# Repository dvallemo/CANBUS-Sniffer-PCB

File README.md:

# CANBUS Sniffer PCB

A compact **USB-to-CAN Bus interface** designed around an **STM32F0 microcontroller** and a **CAN transceiver**. This project was built to practice professional PCB design techniques from schematic capture through PCB layout while following industry design practices.

**Version:** V1.0.0

---

# Features

- USB Type-C Interface
- STM32F0 Microcontroller
- CAN Bus Transceiver
- USB 2.0 Full-Speed Differential Pair
- 3.3V Linear Regulator
- TVS Protection
- Reverse Polarity Protection
- Power LEDs
- CAN Activity LEDs
- SWD Programming Header
- RESET Button
- BOOT Button
- Four Mounting Holes
- Four-Layer PCB

---

# Project Images

## PCB Layout with Ground Pours

---

## 3D Render with Ground Pours

---

## Schematic

---

## Routed PCB

---

## 3D Render

---

# Overview

The goal of this project was to design a complete CAN Bus Sniffer PCB using KiCad while applying professional hardware engineering methodologies.

The board receives power over USB Type-C, regulates the voltage to 3.3V, communicates over a CAN transceiver, and provides an SWD interface for programming and debugging.

Rather than only creating a working PCB, this project focused heavily on layout quality, manufacturability, and signal integrity.

Topics practiced include:

- PCB floorplanning
- Component placement
- USB differential pair routing
- Controlled impedance routing
- Four-layer PCB stackup
- Power distribution
- Ground plane implementation
- Decoupling capacitor placement
- EMI reduction techniques
- Design Rule Checks (DRC)
- Design for Manufacturability (DFM)
- Design for Assembly (DFA)

---

# Hardware Specifications

| Item | Specification |
|------|---------------|
| Microcontroller | STM32F0 Series |
| CAN Transceiver | SN65HVD230 Compatible |
| USB | USB Type-C (USB 2.0 Full Speed) |
| Input Voltage | 5V USB |
| Output Voltage | 3.3V |
| PCB Layers | 4 |
| PCB Thickness | 1.6 mm |
| USB Routing | Controlled Impedance Differential Pair |

---

# PCB Stackup

### Layer 1
- Components
- Signal Routing
- USB Differential Pair

### Layer 2
- Solid Ground Plane

### Layer 3
- Solid Ground Plane

### Layer 4
- Signal Routing
- Power Routing

Using two dedicated internal ground planes provides:

- Continuous return paths
- Reduced EMI
- Improved signal integrity
- Lower ground impedance
- Better high-frequency performance
- Improved power distribution

---

# Engineering Design Decisions

## USB Type-C

USB Type-C was selected for modern compatibility and ease of use.

USB CC pull-down resistors were implemented to correctly identify the board as a USB device.

The USB D+ and D− lines were routed as a differential pair using KiCad's differential pair router.

Special attention was given to:

- Matched trace lengths
- Constant spacing
- Controlled impedance
- Minimal discontinuities
- Smooth routing
- Short path between the connector and downstream circuitry

---

## Differential Pair Routing

Although USB Full-Speed is more forgiving than USB High-Speed, the layout follows professional differential routing practices.

Design considerations included:

- Constant differential spacing
- Matched lengths
- 45° bends
- Minimal skew
- No unnecessary vias
- Short routing distance
- Continuous reference plane underneath the pair

---

## Power Architecture

Power flow:

```text
USB Type-C
    ↓
Protection Circuit
    ↓
Filtering
    ↓
3.3V LDO
    ↓
STM32 + CAN Transceiver
```

Wide power traces were used where appropriate to reduce voltage drop and improve current handling.

---

## Power Integrity

Each power pin is locally decoupled with ceramic capacitors placed as close as possible to the corresponding IC supply pins.

This reduces:

- Supply noise
- Voltage ripple
- Transient voltage drops
- EMI

---

## Grounding Strategy

The board utilizes:

- Layer 2 Solid Ground Plane
- Layer 3 Solid Ground Plane
- Top Ground Pour
- Bottom Ground Pour
- Ground stitching vias

This creates low-impedance return paths and improves signal integrity throughout the design.

The exposed thermal pad underneath the STM32 is connected directly into the internal ground planes through a thermal via.

---

## CAN Interface

The CAN transceiver converts the MCU CAN peripheral into differential CANH and CANL signals suitable for automotive communication.

The layout emphasizes:

- Short routing
- Clean return paths
- Differential signaling
- Noise immunity

---

## Crystal Oscillator

The crystal and its load capacitors were placed immediately adjacent to the MCU oscillator pins.

This minimizes:

- Loop area
- EMI susceptibility
- Clock jitter

---

## Component Placement

Components were grouped by function:

### USB Section
- USB Connector
- ESD Protection
- CC Resistors

### Power Section
- Protection
- LDO
- Filtering
- LEDs

### CAN Section
- CAN Connector
- CAN Transceiver
- Termination Components

### MCU Section
- STM32
- Crystal
- Decoupling
- Programming Header

Keeping functional blocks together improves routing quality and simplifies debugging.

---

# PCB Design Practices

The layout follows several common PCB design guidelines:

- Functional component grouping
- Short decoupling connections
- Short crystal routing
- Controlled impedance USB routing
- Wide power traces
- Ground stitching
- Clean routing
- Minimal unnecessary vias
- Four-layer stackup
- Continuous reference planes
- Full Design Rule Check verification

---

# Software Used

- KiCad 9
- STM32CubeMX
- STM32CubeIDE

---

# Current Status

- ✅ Schematic Complete
- ✅ PCB Layout Complete
- ✅ Four-Layer PCB
- ✅ USB Differential Pair Routed
- ✅ Ground Planes Implemented
- ✅ Design Rule Check Passed
- ✅ 3D Model Generated
- ✅ GitHub Documentation Complete

---

# Future Improvements

- PCB Manufacturing
- Board Bring-up
- Firmware Development
- USB CDC Interface
- CAN Frame Decoder
- Desktop GUI
- Oscilloscope Validation
- Enclosure Design

---

# Lessons Learned

This project provided hands-on experience with:

- USB Type-C hardware implementation
- Controlled impedance routing
- Differential pair routing
- Four-layer PCB stackups
- Ground plane design
- Decoupling strategies
- CAN Bus hardware
- STM32 hardware design
- PCB floorplanning
- PCB routing techniques
- Power integrity
- Signal integrity
- Design Rule Checks
- Design for Manufacturability
- Design for Assembly
- Professional hardware documentation using GitHub

---

# Repository Structure

```text
CANBUS-Sniffer-PCB/
│
├── README.md
├── LICENSE
│
├── Hardware/
│   ├── CAN_BUS_sniffer.kicad_pro
│   ├── CAN_BUS_sniffer.kicad_sch
│   ├── CAN_BUS_sniffer.kicad_pcb
│   └── ...
│
├── images/
│   ├── schematic.png
│   ├── pcb_layout.png
│   ├── pcb_layout_w_gndpours.png
│   ├── pcb_3d.png
│   └── pcb_3d_w_gndpours.png
│
├── Manufacturing/
│
└── Firmware/
```

---

# License

This project is released under the **MIT License**.

---

**Designed by David Valle**  
Electrical Engineer | PCB Design | Embedded Systems

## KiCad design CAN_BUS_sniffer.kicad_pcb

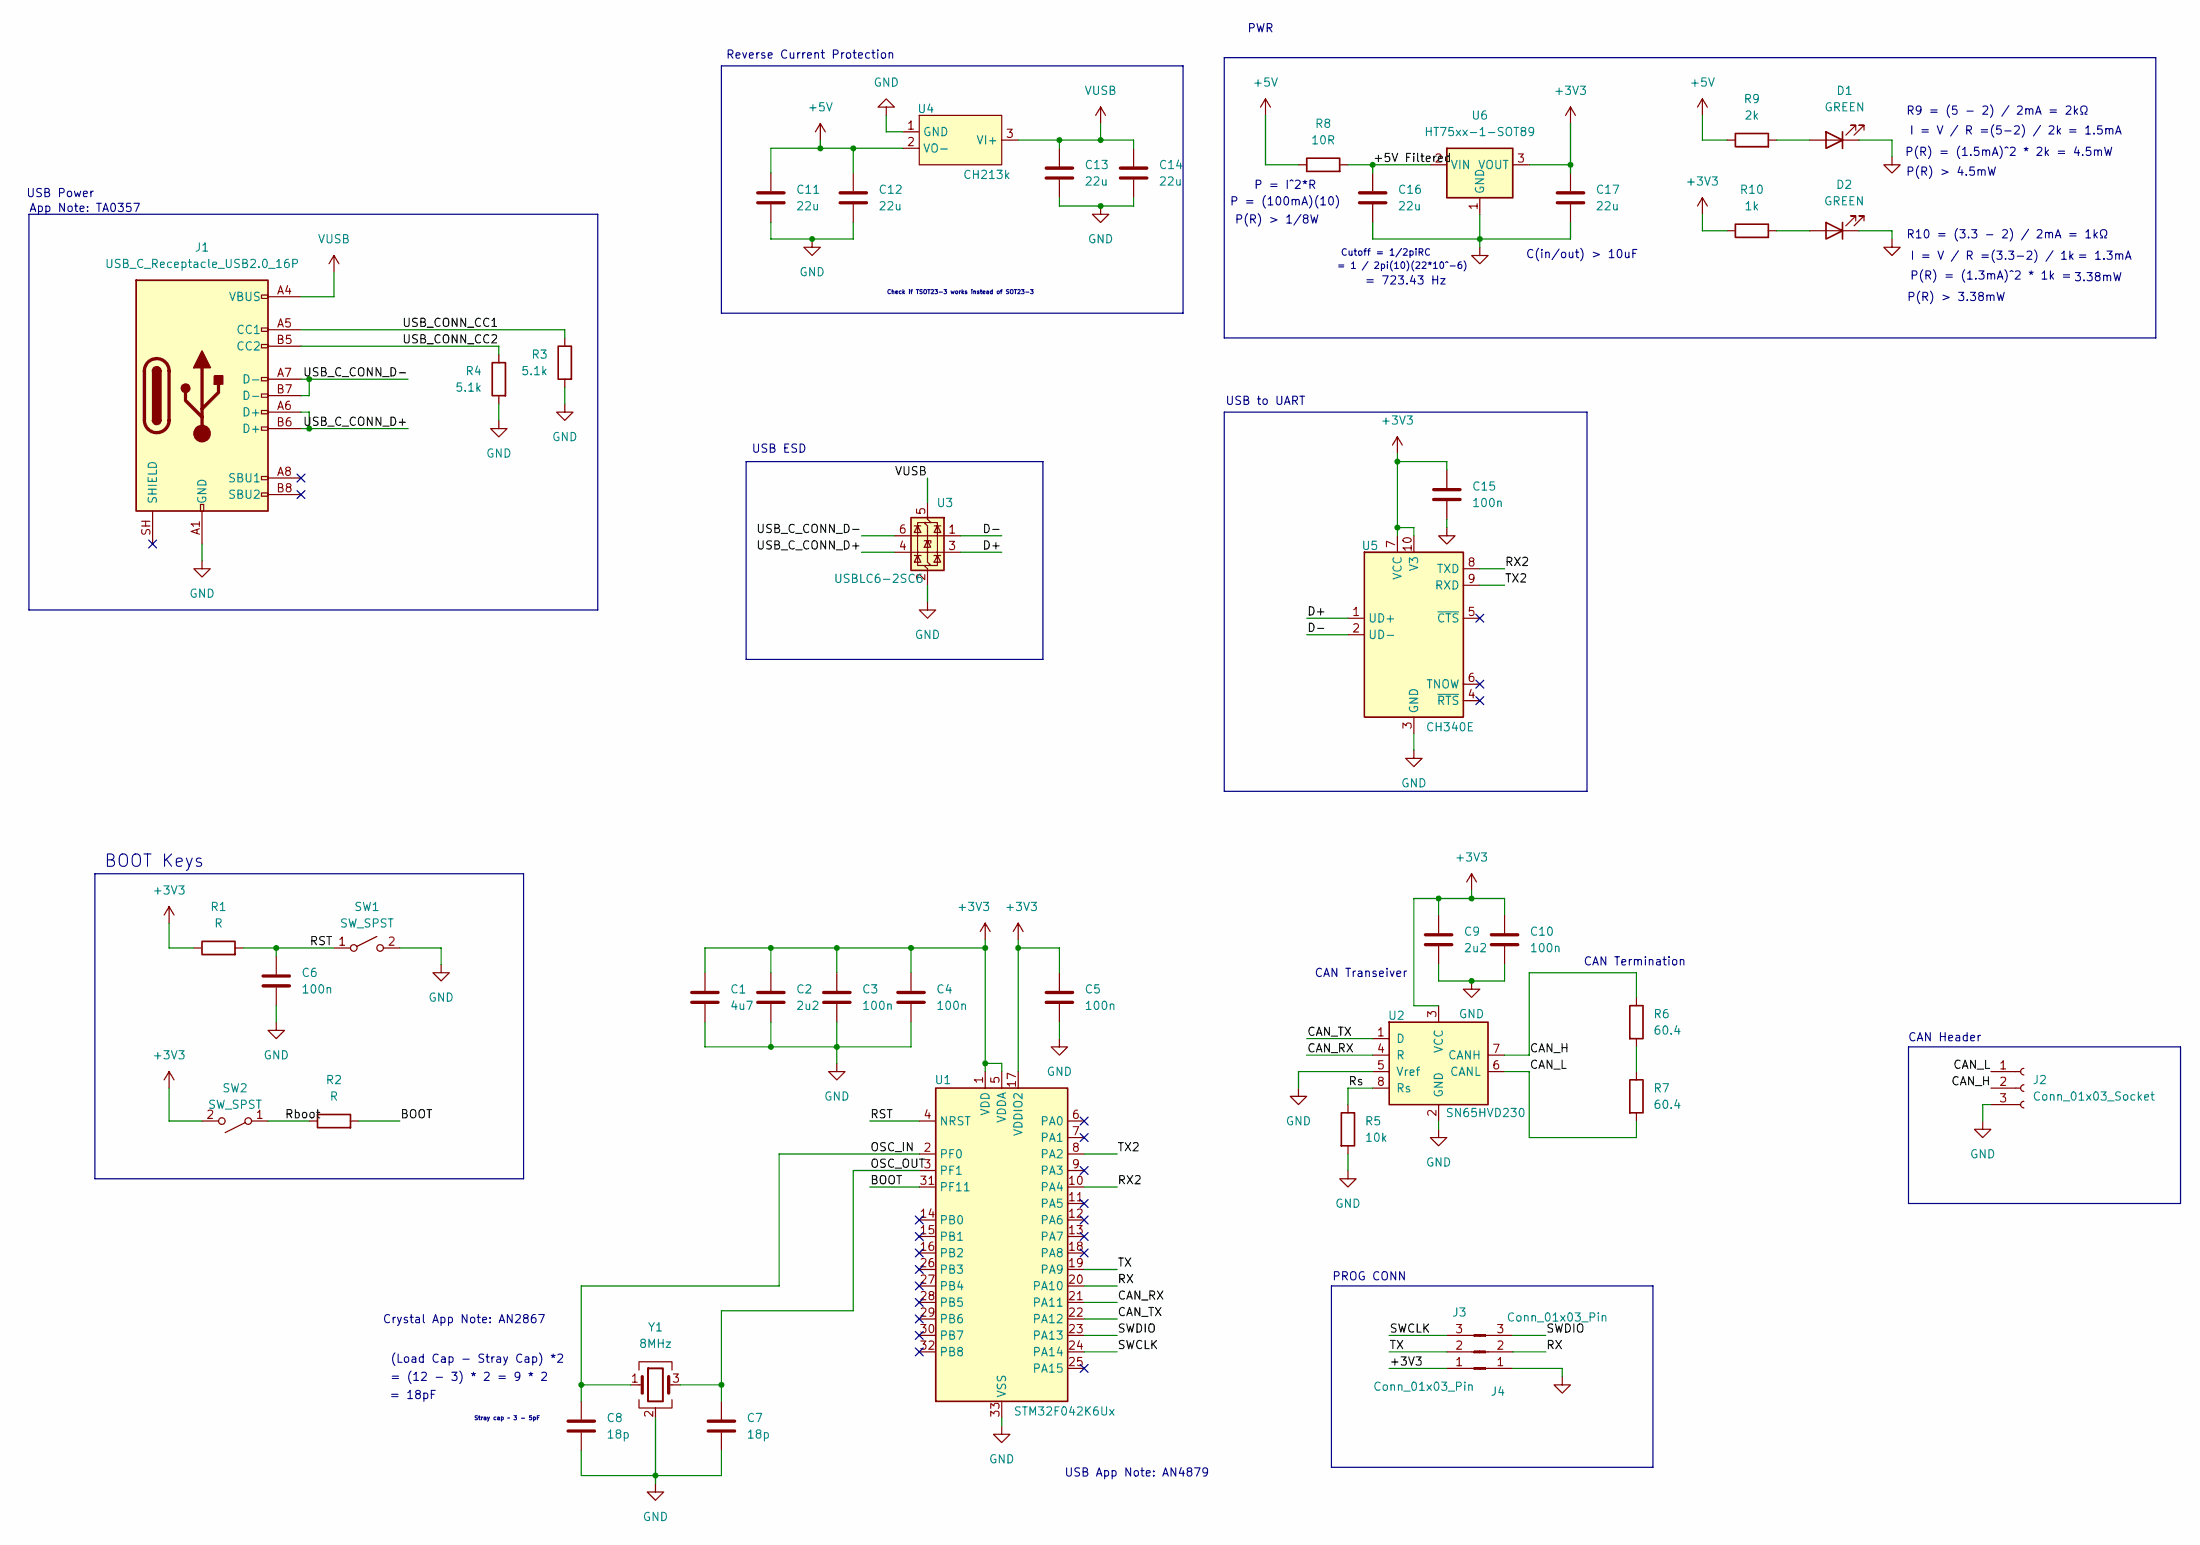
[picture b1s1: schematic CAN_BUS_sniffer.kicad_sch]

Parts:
C1: 4u7; C_0603_1608Metric
C2, C9: 2u2; C_0603_1608Metric
C3, C4, C5, C6, C10, C15: 100n; C_0603_1608Metric
C7, C8: 18p; C_0603_1608Metric
C11, C12, C13, C14, C16, C17: 22u; C_0603_1608Metric
D1, D2: GREEN; LED_0603_1608Metric
J1: USB_C_Receptacle_USB2.0_16P; USB_C_Receptacle_GCT_USB4105-xx-A_16P_TopMnt_Horizontal
J2: Conn_01x03_Socket; JST_PH_S3B-PH-K_1x03_P2.00mm_Horizontal
J3, J4: Conn_01x03_Pin; PinHeader_1x03_P2.54mm_Vertical
R1, R2: R; R_0603_1608Metric
R3, R4: 5.1k; R_0603_1608Metric
R5: 10k; R_0603_1608Metric
R6, R7: 60.4; R_0603_1608Metric
R8: 10R; R_0603_1608Metric
R9: 2k; R_0603_1608Metric
R10: 1k; R_0603_1608Metric
SW1, SW2: SW_SPST; SW_SPST_EVQP0
U1: STM32F042K6Ux; QFN-32-1EP_5x5mm_P0.5mm_EP3.45x3.45mm
U2: SN65HVD230; SOIC-8_3.9x4.9mm_P1.27mm
U3: USBLC6-2SC6; SOT-23-6
U4: CH213k; TSOT-23
U5: CH340E; MSOP-10_3x3mm_P0.5mm
U6: HT75xx-1-SOT89; SOT-89-3
Y1: 8MHz; Crystal_SMD_1210-4Pin_1.2x1.0mm

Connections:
+3V3: C1.1, C2.1, C3.1, C4.1, C5.1, C9.1, C10.1, C15.1, C17.1, J3.1, R1.1, R10.1, SW2.2 (B), U1.1 (VDD), U1.5 (VDDA), U1.17 (VDDIO2), U2.3 (VCC), U5.7 (VCC), U5.10 (V3), U6.3 (VOUT)
+5V: C11.1, C12.1, R8.1, R9.1, U4.2 (VO-)
/+5V Filtered: C16.1, R8.2, U6.2 (VIN)
/BOOT: R2.2, U1.31 (PF11)
/CAN_H: J2.2, R6.1, U2.7 (CANH)
/CAN_L: J2.1, R7.2, U2.6 (CANL)
/CAN_RX: U1.21 (PA11), U2.4 (R)
/CAN_TX: U1.22 (PA12), U2.1 (D)
/D+: U3.3 (I/O2), U5.1 (UD+)
/D-: U3.1 (I/O1), U5.2 (UD-)
/OSC_IN: C8.1, U1.2 (PF0), Y1.1
/OSC_OUT: C7.1, U1.3 (PF1), Y1.3
/RST: C6.1, R1.2, SW1.1 (A), U1.4 (NRST)
/RX: J4.2, U1.20 (PA10)
/RX2: U1.10 (PA4), U5.8 (TXD)
/Rboot: R2.1, SW2.1 (A)
/Rs: R5.1, U2.8 (Rs)
/SWCLK: J3.3, U1.24 (PA14)
/SWDIO: J4.3, U1.23 (PA13)
/TX: J3.2, U1.19 (PA9)
/TX2: U1.8 (PA2), U5.9 (RXD)
/USB_CONN_CC1: J1.A5 (CC1), R3.1
/USB_CONN_CC2: J1.B5 (CC2), R4.1
/USB_C_CONN_D+: J1.A6 (D+), J1.B6 (D+), U3.4 (I/O2)
/USB_C_CONN_D-: J1.A7 (D-), J1.B7 (D-), U3.6 (I/O1)
GND: C1.2, C2.2, C3.2, C4.2, C5.2, C6.2, C7.2, C8.2, C9.2, C10.2, C11.2, C12.2, C13.2, C14.2, C15.2, C16.2, C17.2, D1.1 (K), D2.1 (K), J1.A1 (GND), J1.A12 (GND), J1.B1 (GND), J1.B12 (GND), J2.3, J4.1, R3.2, R4.2, R5.2, SW1.2 (B), U1.33 (VSS), U2.2 (GND), U2.5 (Vref), U3.2 (GND), U4.1 (GND), U5.3 (GND), U6.1 (GND), Y1.2 (G), Y1.4 (G)
unnamed: D1.2 (A), R9.2
unnamed: D2.2 (A), R10.2
unnamed: R6.2, R7.1
VUSB: C13.1, C14.1, J1.A4 (VBUS), J1.A9 (VBUS), J1.B4 (VBUS), J1.B9 (VBUS), U3.5 (VBUS), U4.3 (VI+)

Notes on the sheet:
= (12 - 3) * 2 = 9 * 2
P(R) = (1.3mA)^2 * 1k =
P = (100mA)(10)
CAN Header
App Note: TA0357
I = V / R =(5-2) / 2k
USB Power
I = V / R =(3.3-2) / 1k
= 723.43 Hz
P(R) = (1.5mA)^2 * 2k = 4.5mW
PWR
R9 = (5 - 2) / 2mA = 2kΩ
CAN Termination
CAN Transeiver
PROG CONN
= 18pF
Reverse Current Protection
Check if TSOT23-3 works instead of SOT23-3
R10 = (3.3 - 2) / 2mA = 1kΩ
= 1.3mA
USB App Note: AN4879
Cutoff = 1/2piRC
= 1 / 2pi(10)(22*10^-6)
Crystal App Note: AN2867
P(R) > 4.5mW
USB to UART
P = I^2*R
Stray cap ~ 3 - 5pF
= 1.5mA
USB ESD
P(R) > 1/8W
(Load Cap - Stray Cap) *2
C(in/out) > 10uF
BOOT Keys
3.38mW
P(R) > 3.38mW

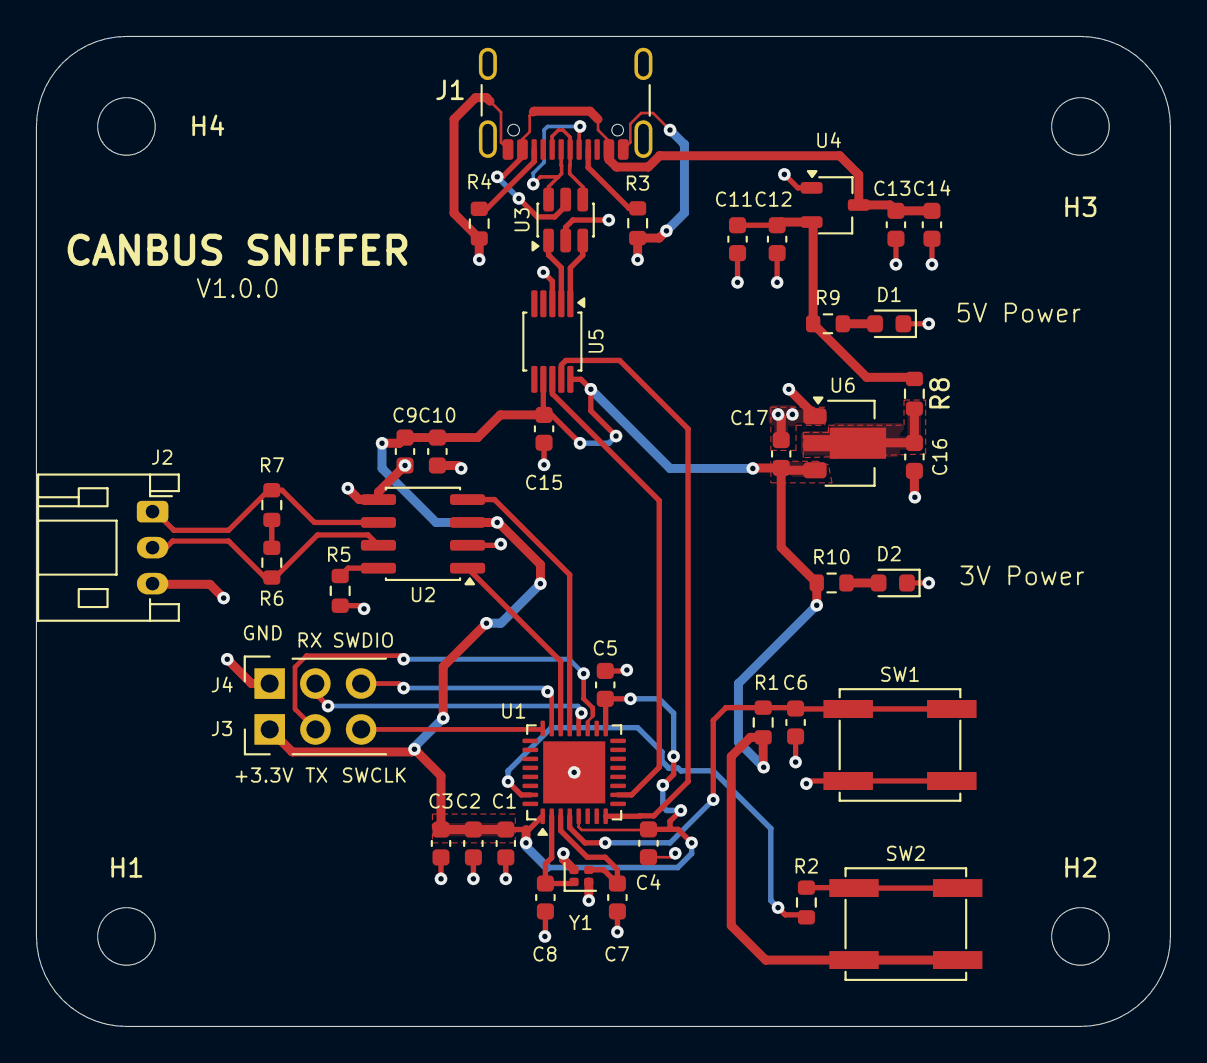
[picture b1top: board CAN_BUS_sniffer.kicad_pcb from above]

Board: 4 copper layers, 63.0 x 55.0 mm, 46 parts (0 on the bottom side), 30 nets.

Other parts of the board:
H1, H2, H3, H4: MountingHole; MountingHole_3.2mm_M3_ISO7380

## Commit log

2026-06-29 Create test
2026-06-29 Rename Screenshot 2026-06-29 161404.png to pcb_layout.png
2026-06-29 Rename Screenshot 2026-06-29 161421.png to pcb_3d.png
2026-06-30 adding layout design improvement
2026-06-30 Rename Screenshot 2026-06-29 210212.png to pcb_layout_w_gndpours.png
2026-06-30 Rename Screenshot 2026-06-29 210225.png to pcb_3d_w_gndpours.png
2026-06-30 Rename Screenshot 2026-06-29 210920.png to schematic.png
